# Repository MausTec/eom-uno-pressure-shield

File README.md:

# eom-uno-pressure-shield

This pressure logger shield features a 50 or 100KPa pressure sensor with a 3.5mm barbed inlet, a bar graph readout, variable gain, 
a record start/stop button and an external hookup to a trigger for marking your logs.

Learning topics covered in this kit:

- Analog sampling & operational amplifiers
- LED matrix charlieplexing

Soldering Skill: 2/10

- Through Hole min. pitch: 0.1"
- Surface Mount min. pitch: 0.1"
- IC: Socketed

## Assembly Instructions

Forthcoming

## Theory of Operation

Forthcoming

## Assembly Kits & Builds

Assembly kits and completed builds can be purchased from Maus-Tec's online store:

https://maustec.io/products/arduino-pressure-logger-shield

## License

Hardware designs and schematics are copyright &copy;2020-2021 Maus-Tec LLC. Use of IP in this repository is licensed under 
Creative Commons Attribution-NonCommmercial-ShareAlike 4.0 International. Click the badge above for details.

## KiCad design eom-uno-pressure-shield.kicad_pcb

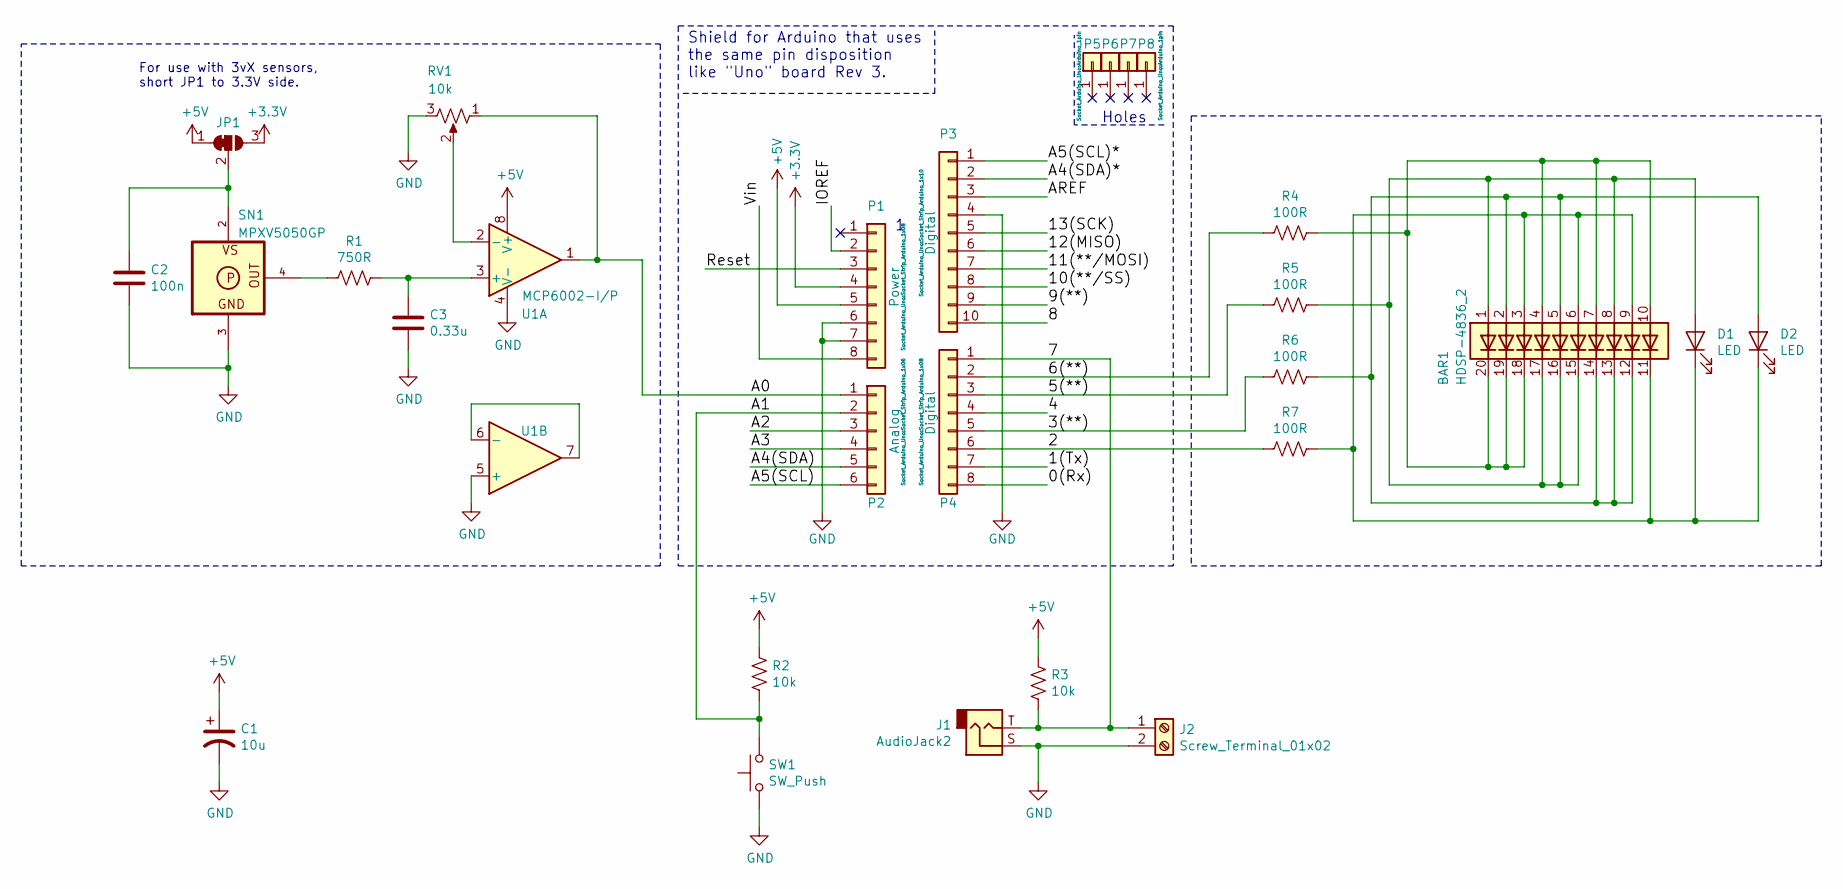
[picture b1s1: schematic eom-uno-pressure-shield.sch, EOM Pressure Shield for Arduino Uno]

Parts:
BAR1: HDSP-4836_2; HDSP-4836
C1: 10u; CP_Radial_D6.3mm_P2.50mm
C2: 100n; C_Disc_D5.0mm_W2.5mm_P2.50mm
C3: 0.33u; C_Disc_D5.0mm_W2.5mm_P2.50mm
D1, D2: LED; LED_D3.0mm
J1: AudioJack2; Jack_3.5mm_CUI_SJ1-3533NG_Horizontal
J2: Screw_Terminal_01x02; TerminalBlock_bornier-2_P5.08mm
JP1: SolderJumper_3_Bridged12; SolderJumper-3_P1.3mm_Bridged12_Pad1.0x1.5mm_NumberLabels
P1: Power; Socket_Strip_Arduino_1x08
P2: Analog; Socket_Strip_Arduino_1x06
P3: Digital; Socket_Strip_Arduino_1x10
P4: Digital; Socket_Strip_Arduino_1x08
P5, P6, P7, P8: CONN_01X01; Arduino_1pin
R1: 750R; R_Axial_DIN0207_L6.3mm_D2.5mm_P10.16mm_Horizontal
R2, R3: 10k; R_Axial_DIN0207_L6.3mm_D2.5mm_P10.16mm_Horizontal
R4, R5, R6, R7: 100R; R_Axial_DIN0207_L6.3mm_D2.5mm_P10.16mm_Horizontal
RV1: 10k; Potentiometer_Bourns_3386P_Vertical
SN1: MPXV5050GP; SOP8-1369
SW1: SW_Push; SW_PUSH_6mm
U1: MCP6002-I/P; DIP-8_W7.62mm_LongPads

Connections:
+3V3: JP1.3 (B), P1.4
+5V: C1.1, JP1.1 (A), P1.5, R2.1, R3.1, U1.8 (V+)
/0(Rx): P4.8
/1(Tx): P4.7
/2: P4.6, R7.2
/3(**): P4.5, R6.2
/4: P4.4
/5(**): P4.3, R5.2
/6(**): P4.2, R4.2
/7: J1.T, J2.1, P4.1, R3.2
/8: P3.10
/9(**): P3.9
/10(**/SS): P3.8
/11(**/MOSI): P3.7
/12(MISO): P3.6
/13(SCK): P3.5
/A0: P2.1, RV1.1, U1.1
/A1: P2.2, R2.2, SW1.2
/A2: P2.3
/A3: P2.4
/A4(SDA): P2.5
/A4(SDA)*: P3.2
/A5(SCL): P2.6
/A5(SCL)*: P3.1
/AREF: P3.3
/IOREF: P1.2
/Reset: P1.3
/Vin: P1.8
GND: C1.2, C2.2, C3.2, J1.S, J2.2, P1.6, P1.7, P3.4, RV1.3, SN1.3, SW1.1, U1.4 (V-), U1.5 (+)
unnamed: BAR1.1 (A), BAR1.8 (A), BAR1.15 (K), BAR1.16 (K), BAR1.17 (K), D1.2 (A), R5.1
unnamed: BAR1.4 (A), BAR1.7 (A), BAR1.10 (A), BAR1.18 (K), BAR1.19 (K), BAR1.20 (K), R4.1
unnamed: BAR1.3 (A), BAR1.6 (A), BAR1.9 (A), BAR1.11 (K), D1.1 (K), D2.1 (K), R7.1
unnamed: BAR1.2 (A), BAR1.5 (A), BAR1.12 (K), BAR1.13 (K), BAR1.14 (K), D2.2 (A), R6.1
unnamed: C2.1, JP1.2 (C), SN1.2
unnamed: C3.1, R1.1, U1.3 (+)
unnamed: R1.2, SN1.4
unnamed: RV1.2, U1.2 (-)
unnamed: U1.6 (-), U1.7

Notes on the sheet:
Holes
Shield for Arduino that uses the same pin disposition like "Uno" board Rev 3.
For use with 3vX sensors, short JP1 to 3.3V side.

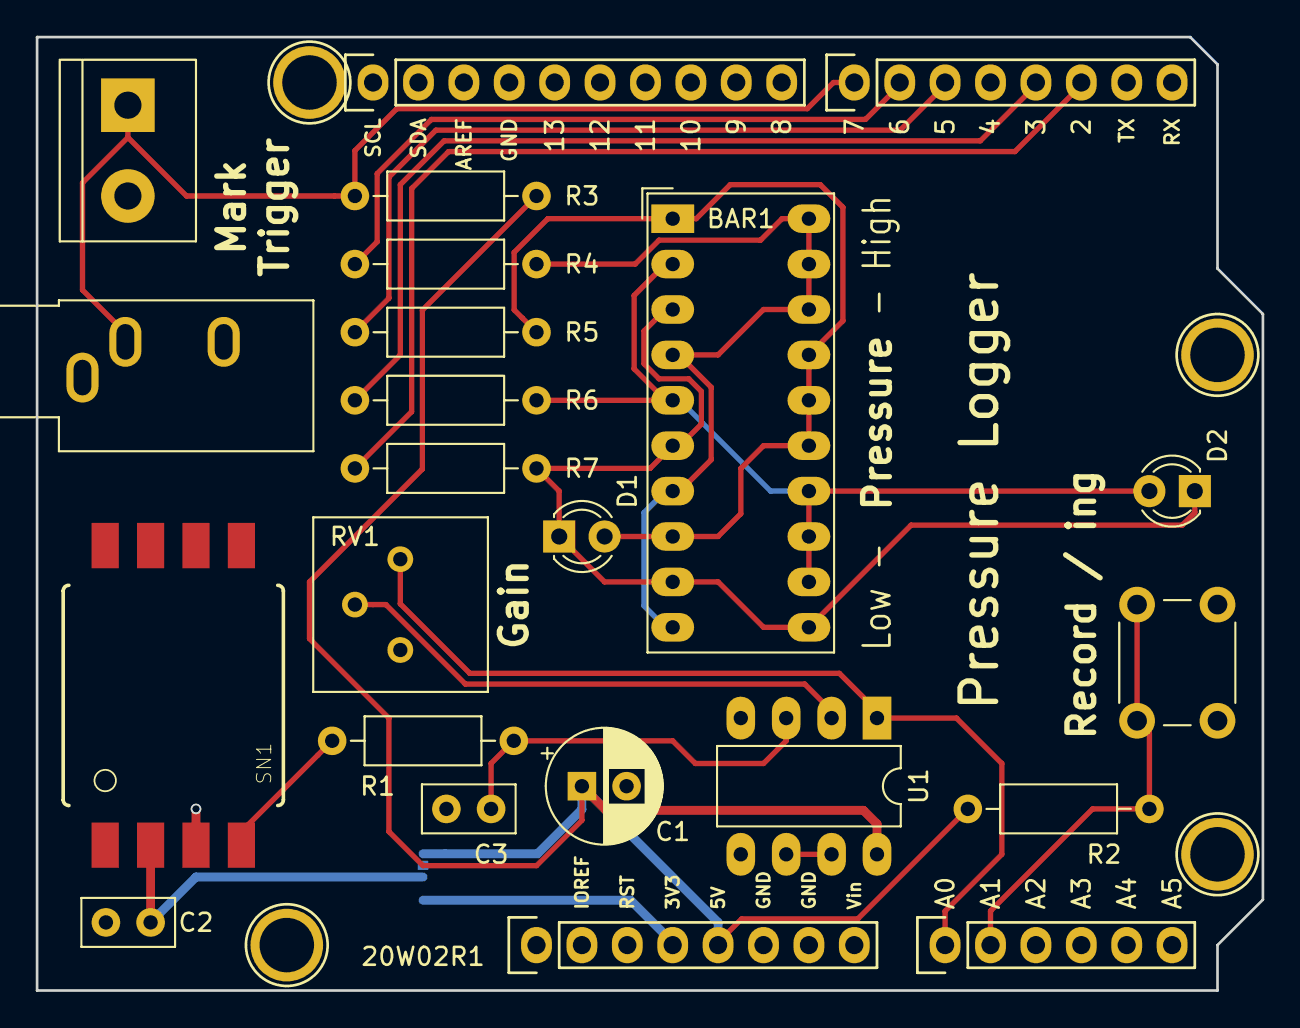
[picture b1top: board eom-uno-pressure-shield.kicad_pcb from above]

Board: 2 copper layers, 68.6 x 53.3 mm, 28 parts (1 on the bottom side), 19 nets.

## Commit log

2021-01-10 Add schematic.pdf
    Need proper organization for KiCad + Arduino projects.
2021-02-22 Update LICENSE
